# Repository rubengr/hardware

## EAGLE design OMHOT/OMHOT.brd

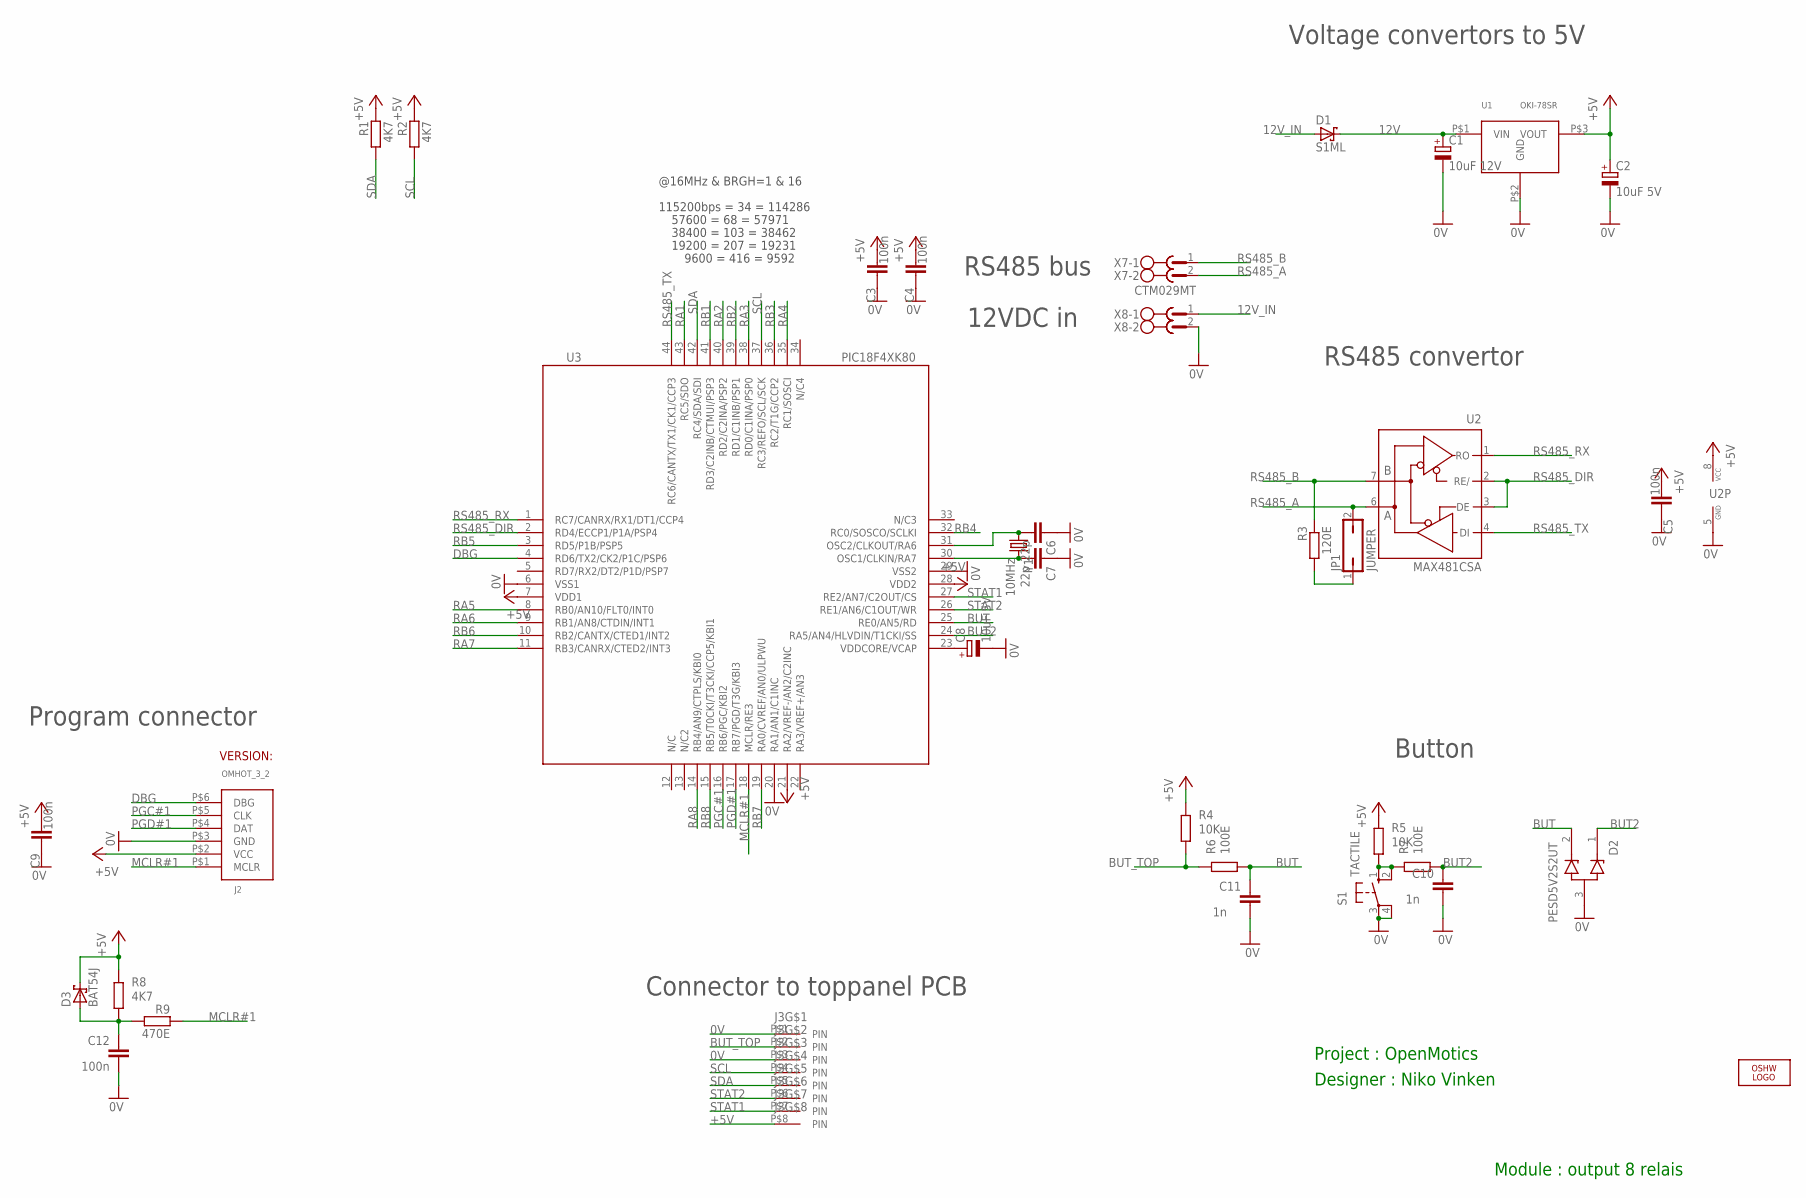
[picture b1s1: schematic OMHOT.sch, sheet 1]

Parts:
C1: 10uF 12V; 085CS_1AR
C2, C8: 10uF 5V; 085CS_1AR
C3, C4, C5, C9, C12: 100n; C0603
C6, C7: 22p; C0603
C10, C11: 1n; C0603
D1: S1ML; SOD123FL
D2: PESD5V2S2UT; SOT23
D3: BAT54J; SOD323_REFLOW
J2: PROG_CON; PROG_CON_WITH_VERSION
J3: 8PIN_CON_AMP
JP1: JUMPER; JP1
LOGO2: OSHW_LOGO_FILLX0150-NT; OSHW_FILLX150_NOTEXT
R1, R2, R8: 4K7; R0603
R3: 120E; R1206
R4, R5: 10K; R0603
R6, R7: 100E; R0603
R9: 470E; R0603
S1: TACTILE; B3F-10XX
U1: OKI-78SR
U2: MAX481CSA; SO08
U3: PIC18F4XK80; TQFP44
X7, X8: CTM029MT
Y1: 10MHz; SM49

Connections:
0V: C1.-, C2.-, C3.2, C4.2, C5.2, C6.1, C7.1, C8.-, C9.2, C10.1, C11.1, C12.1, D2.3, J2.P$3 (GND), J3.P$1, J3.P$3, S1.3, S1.4 (P1), U1.P$2 (GND), U2.5 (GND), U3.6 (VSS1), U3.20 (RA1/AN1/C1INC), U3.29 (VSS2), X8.2; also elsewhere on the board
12V: C1.+, D1.C, U1.P$1 (VIN)
12V_IN: D1.A, X8.1
+5V: C2.+, C3.1, C4.1, C5.1, C9.1, D3.1, J2.P$2 (VCC), J3.P$8, R1.1, R2.1, R4.2, R5.2, R8.2, U1.P$3 (VOUT), U2.8 (VCC), U3.7 (VDD1), U3.21 (RA2/VREF-/AN2/C2INC), U3.28 (VDD2); also elsewhere on the board
BUT: C11.2, D2.2, R6.1, U3.25 (RE0/AN5/RD)
BUT2: C10.2, D2.1, R7.1, U3.24 (RA5/AN4/HLVDIN/T1CKI/SS)
BUT3: R5.1, R7.2, S1.1 (S), S1.2 (S1)
BUT_TOP: J3.P$2, R4.1, R6.2
DBG: J2.P$6 (DBG), U3.4 (RD6/TX2/CK2/P1C/PSP6)
MCLR#1: J2.P$1 (MCLR), R9.1, U3.18 (MCLR/RE3)
unnamed: C6.2, U3.31 (OSC2/CLKOUT/RA6), Y1.1
unnamed: C7.2, U3.30 (OSC1/CLKIN/RA7), Y1.2
unnamed: C8.+, U3.23 (VDDCORE/VCAP)
unnamed: JP1.1, R3.2
unnamed: C12.2, D3.2, R8.1, R9.2
PGC#1: J2.P$5 (CLK), U3.16 (RB6/PGC/KBI2)
PGD#1: J2.P$4 (DAT), U3.17 (RB7/PGD/T3G/KBI3)
RA1: U3.43 (RC5/SDO); also elsewhere on the board
RA2: U3.40 (RD2/C2INA/PSP2); also elsewhere on the board
RA3: U3.38 (RD0/C1INA/PSP0); also elsewhere on the board
RA4: U3.35 (RC1/SOSCI); also elsewhere on the board
RA5: U3.8 (RB0/AN10/FLT0/INT0); also elsewhere on the board
RA6: U3.9 (RB1/AN8/CTDIN/INT1); also elsewhere on the board
RA7: U3.11 (RB3/CANRX/CTED2/INT3); also elsewhere on the board
RA8: U3.14 (RB4/AN9/CTPLS/KBI0); also elsewhere on the board
RB1: U3.41 (RD3/C2INB/CTMUI/PSP3); also elsewhere on the board
RB2: U3.39 (RD1/C1INB/PSP1); also elsewhere on the board
RB3: U3.36 (RC2/T1G/CCP2); also elsewhere on the board
RB4: U3.32 (RC0/SOSCO/SCLKI); also elsewhere on the board
RB5: U3.3 (RD5/P1B/PSP5); also elsewhere on the board
RB6: U3.10 (RB2/CANTX/CTED1/INT2); also elsewhere on the board
RB7: U3.19 (RA0/CVREF/AN0/ULPWU); also elsewhere on the board
RB8: U3.15 (RB5/T0CKI/T3CKI/CCP5/KBI1); also elsewhere on the board
RS485_A: JP1.2, U2.6 (A), X7.2
RS485_B: R3.1, U2.7 (B), X7.1
RS485_DIR: U2.2 (RE/), U2.3 (DE), U3.2 (RD4/ECCP1/P1A/PSP4)
RS485_RX: U2.1 (RO), U3.1 (RC7/CANRX/RX1/DT1/CCP4)
RS485_TX: U2.4 (DI), U3.44 (RC6/CANTX/TX1/CK1/CCP3)
SCL: J3.P$4, R2.2, U3.37 (RC3/REFO/SCL/SCK)
SDA: J3.P$5, R1.2, U3.42 (RC4/SDA/SDI)
STAT1: J3.P$7, U3.27 (RE2/AN7/C2OUT/CS)
STAT2: J3.P$6, U3.26 (RE1/AN6/C1OUT/WR)

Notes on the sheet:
Project : OpenMotics
Designer : Niko Vinken
Module : output 8 relais
Program connector
RS485 convertor
Connector to toppanel PCB
Button
@16MHz & BRGH=1 & 16
115200bps = 34 = 114286
38400 = 103 = 38462
9600 = 416 = 9592
19200 = 207 = 19231
57600 = 68 = 57971
Voltage convertors to 5V
RS485 bus
12VDC in

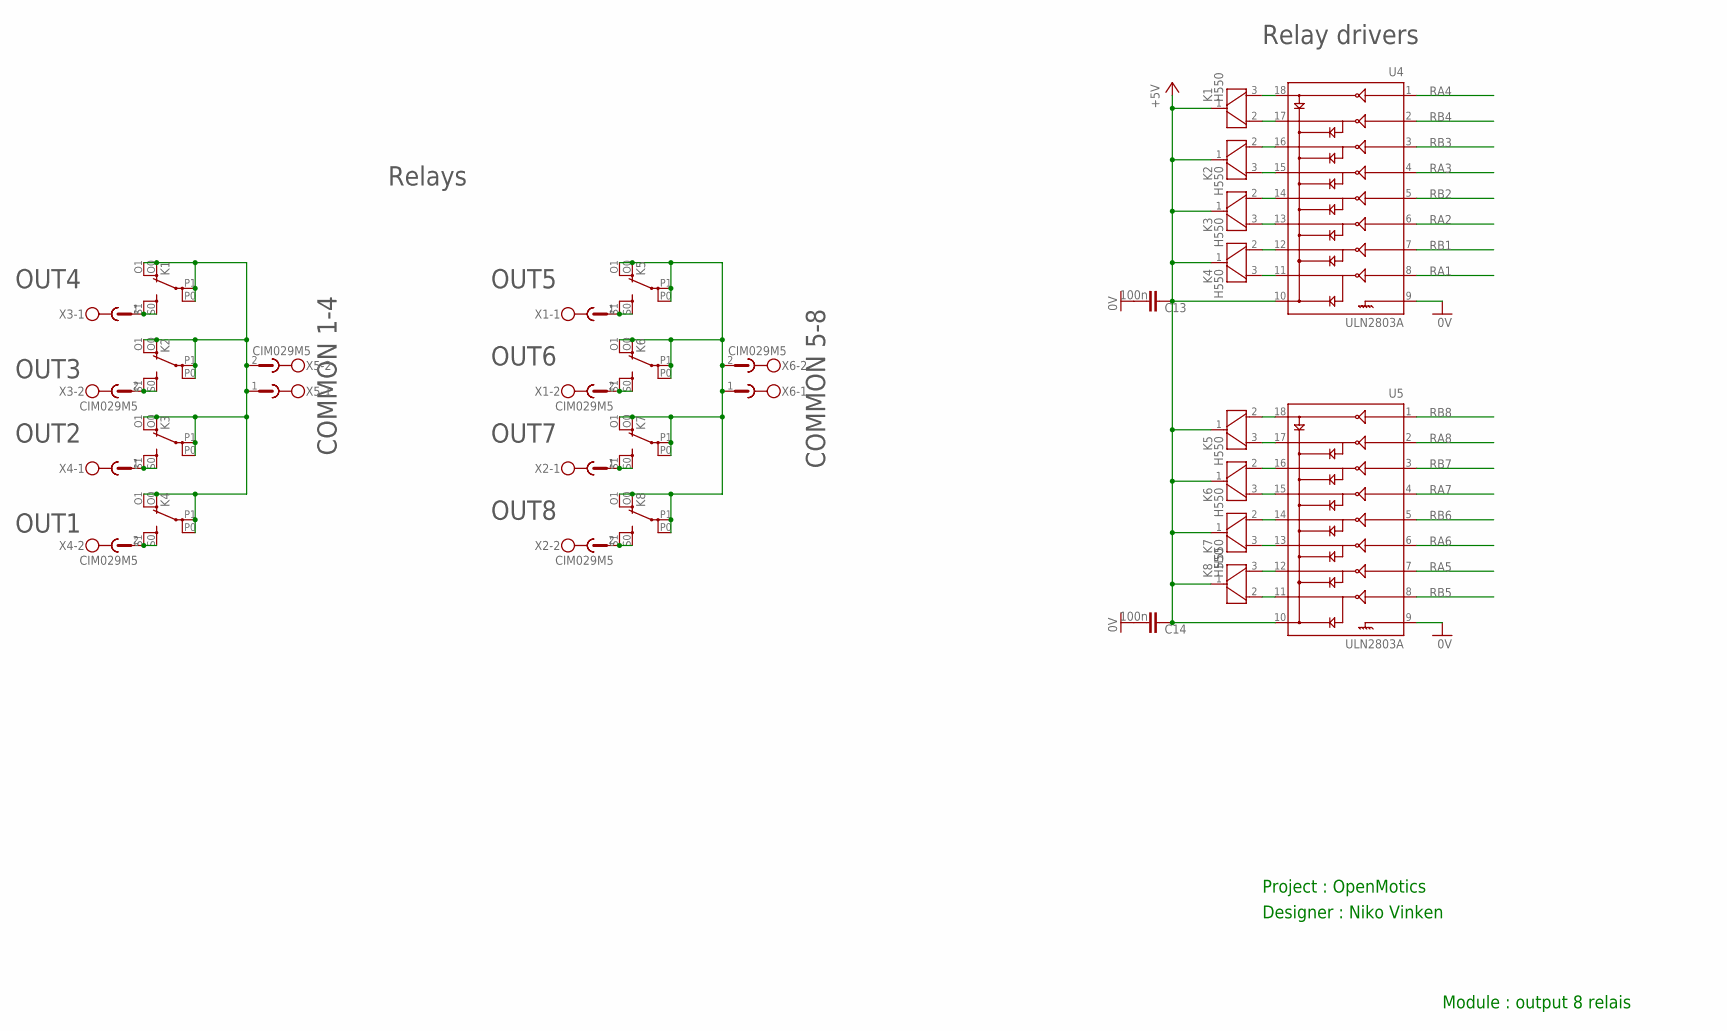
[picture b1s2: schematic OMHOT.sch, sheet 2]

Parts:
C13, C14: 100n; C0603
K1, K2, K3, K4, K5, K6, K7, K8: H550
U4, U5: ULN2803A; SOIC18
X1, X2, X3, X4, X5, X6: CIM029M5

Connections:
0V: C13.1, C14.1, U4.9, U5.9; also elsewhere on the board
+5V: C13.2, C14.2, K1.1, K2.1, K3.1, K4.1, K5.1, K6.1, K7.1, K8.1, U4.10, U5.10; also elsewhere on the board
unnamed: K5.S0 (S), K5.S1 (S), X1.1
unnamed: K3.S0 (S), K3.S1 (S), X4.1
unnamed: K4.S0 (S), K4.S1 (S), X4.2
unnamed: K6.S0 (S), K6.S1 (S), X1.2
unnamed: K4.3, U4.11
unnamed: K4.2, U4.12
unnamed: K1.S0 (S), K1.S1 (S), X3.1
unnamed: K3.3, U4.13
unnamed: K7.S0 (S), K7.S1 (S), X2.1
unnamed: K8.S0 (S), K8.S1 (S), X2.2
unnamed: K1.O0 (O), K1.O1 (O), K1.P0, K1.P1, K2.O0 (O), K2.O1 (O), K2.P0, K2.P1, K3.O0 (O), K3.O1 (O), K3.P0, K3.P1, K4.O0 (O), K4.O1 (O), K4.P0, K4.P1, X5.1, X5.2
unnamed: K2.S0 (S), K2.S1 (S), X3.2
unnamed: K3.2, U4.14
unnamed: K2.3, U4.15
unnamed: K2.2, U4.16
unnamed: K1.3, U4.18
unnamed: K1.2, U4.17
unnamed: K5.3, U5.17
unnamed: K5.O0 (O), K5.O1 (O), K5.P0, K5.P1, K6.O0 (O), K6.O1 (O), K6.P0, K6.P1, K7.O0 (O), K7.O1 (O), K7.P0, K7.P1, K8.O0 (O), K8.O1 (O), K8.P0, K8.P1, X6.1, X6.2
unnamed: K5.2, U5.18
unnamed: K6.3, U5.15
unnamed: K6.2, U5.16
unnamed: K7.3, U5.13
unnamed: K7.2, U5.14
unnamed: K8.3, U5.12
unnamed: K8.2, U5.11
RA1: U4.8; also elsewhere on the board
RA2: U4.6; also elsewhere on the board
RA3: U4.4; also elsewhere on the board
RA4: U4.1; also elsewhere on the board
RA5: U5.7; also elsewhere on the board
RA6: U5.6; also elsewhere on the board
RA7: U5.4; also elsewhere on the board
RA8: U5.2; also elsewhere on the board
RB1: U4.7; also elsewhere on the board
RB2: U4.5; also elsewhere on the board
RB3: U4.3; also elsewhere on the board
RB4: U4.2; also elsewhere on the board
RB5: U5.8; also elsewhere on the board
RB6: U5.5; also elsewhere on the board
RB7: U5.3; also elsewhere on the board
RB8: U5.1; also elsewhere on the board

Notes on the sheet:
Project : OpenMotics
Designer : Niko Vinken
Module : output 8 relais
Relay drivers
Relays
OUT4
OUT3
OUT2
OUT1
OUT5
OUT6
OUT7
OUT8
COMMON 1-4
COMMON 5-8

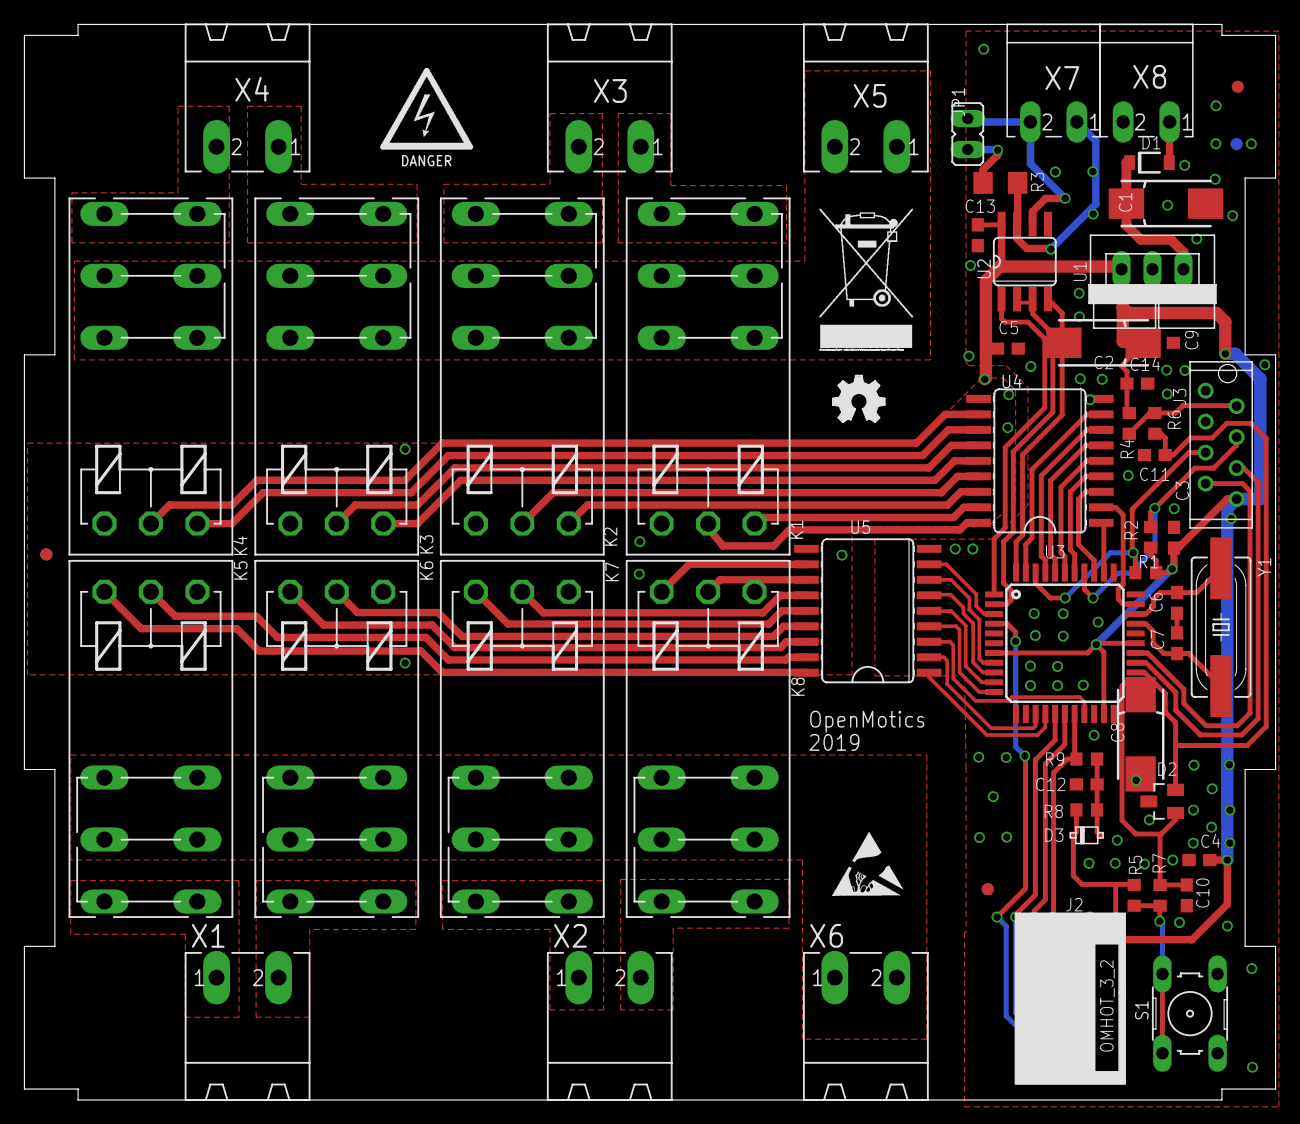
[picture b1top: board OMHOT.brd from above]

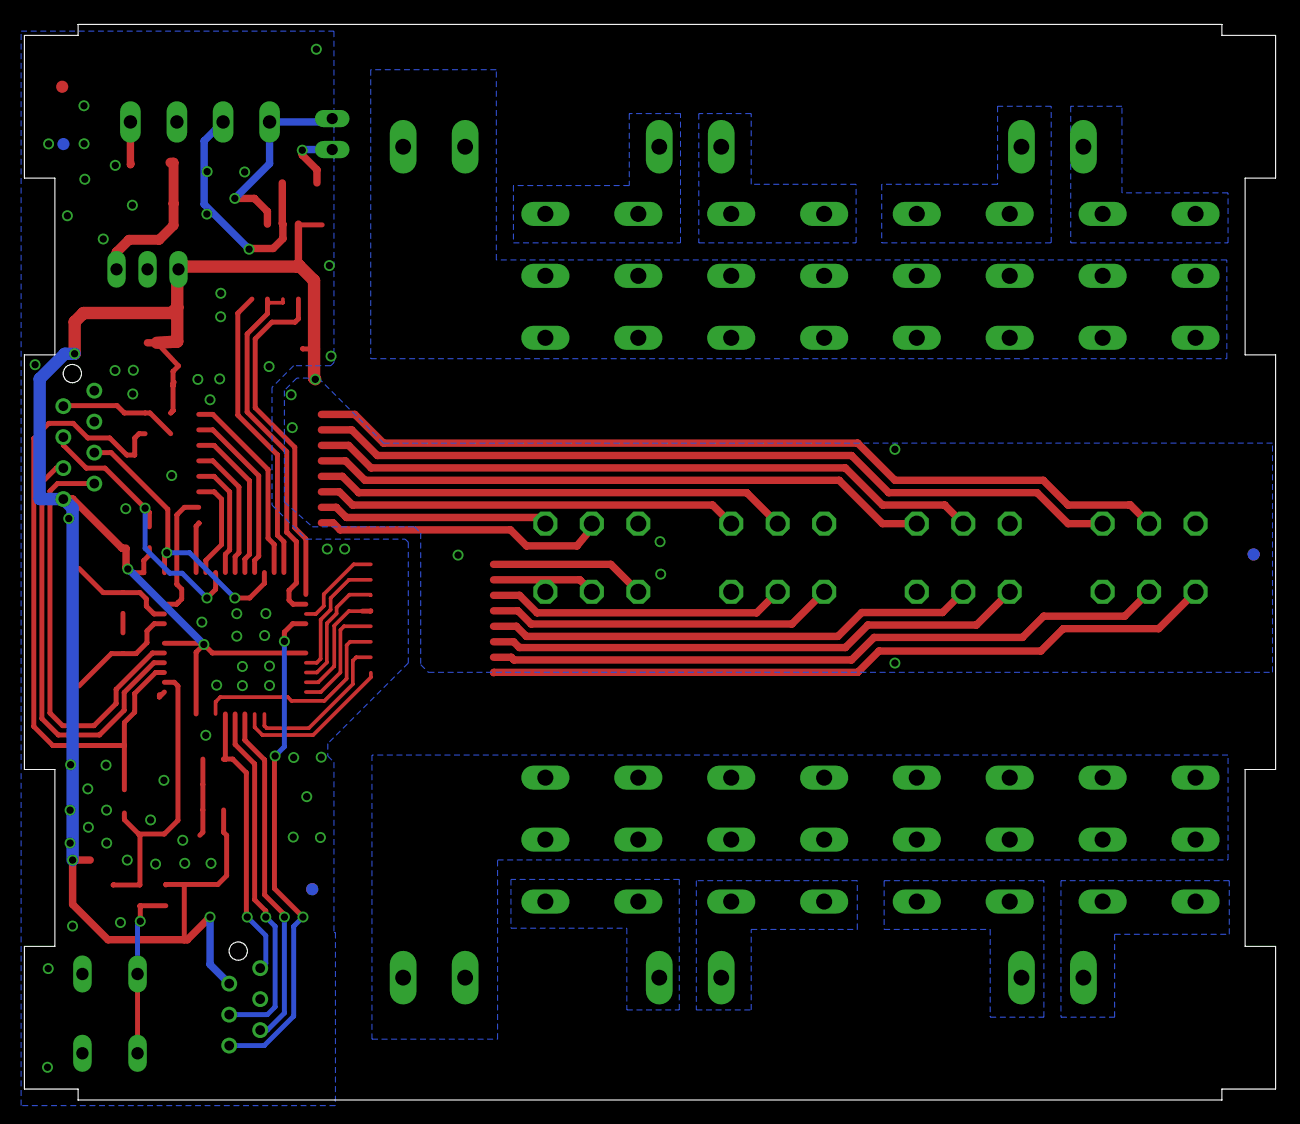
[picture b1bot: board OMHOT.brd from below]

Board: 2 copper layers, 102.6 x 88.2 mm, 63 parts (3 on the bottom side), 68 nets.

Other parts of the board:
U$1, U$2, U$3, U$5, U$6, U$12: FIDUCIAL_G10
U$4: CNMB/6; CNMB/6-
U$8: DISPOSAL-SYMBOL; DISPOSAL
U$10: ESD
U$11: HIGH-VOLTAGE

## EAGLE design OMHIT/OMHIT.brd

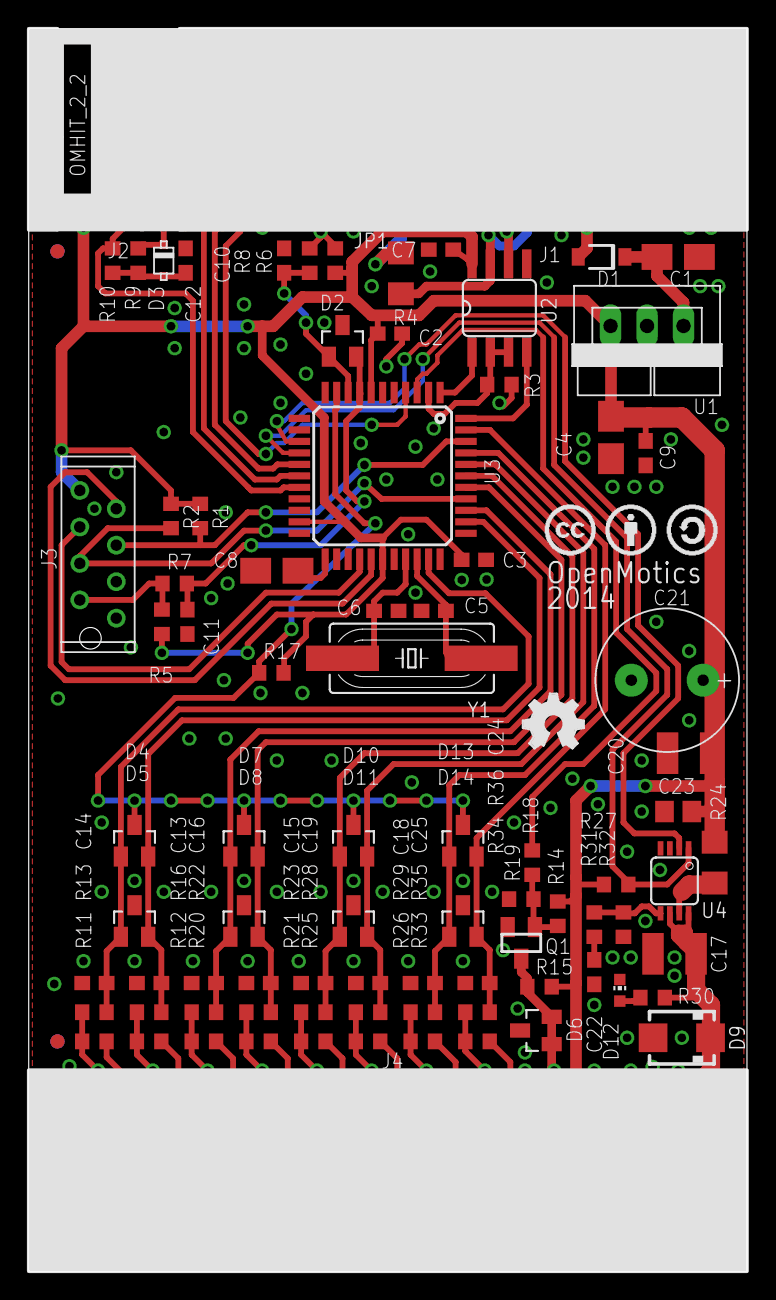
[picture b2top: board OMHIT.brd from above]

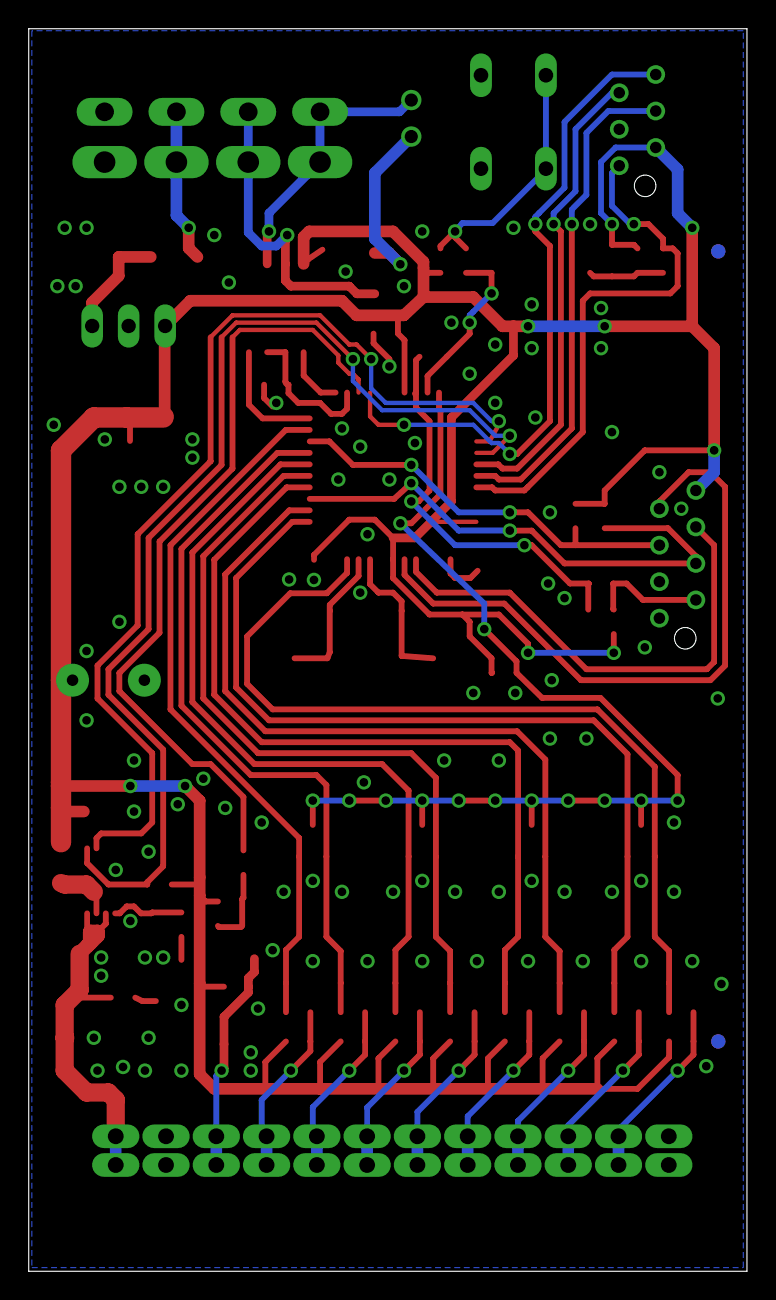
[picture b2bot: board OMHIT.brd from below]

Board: 2 copper layers, 50.0 x 86.5 mm, 94 parts (2 on the bottom side), 53 nets.

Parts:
C1: 10uF 12V; A3216-18W
C2, C3, C7, C9, C12, C22: 100n; C0603
C4: 10uF 5V; A3216-18W
C5, C6: 22p; C0603
C8: 10u; A3216-18W
C10, C11, C13, C14, C15, C16, C18, C19, C24, C25: 1n; C0603
C17, C20: 22uF; C1210K
C21: 1000uF; ELCO10MM
C23: 1u; C0805
D1: S1ML; SOD123FL
D2, D5, D8, D11, D14: PESD5V2S2UT; SOT23
D3: BAT54J; SOD323_REFLOW
D4, D7, D10, D13: BAT54A; SOT23
D6: PESD3V3S2UAT; SOT23
D9: SMAJ6.0A; SMA
D12: LGQ971; CHIP-LED0603
J1: PTDA_1.5_4-PH_5.0; PTDA_1.5_X-PH_5.0
J2: PROG_CON_WITH_VERSION
J3: 8PIN_CON_AMP
J4: PTDA_1.5_12-PH_3.5; PTDA_1.5_X-PH_3.5
JP1: JP1S
LOGO2: OSHW_LOGO_FILLX0150-NT; OSHW_FILLX150_NOTEXT
Q1: PMBF170; SUPER-SOT3
R1, R2, R9: 4K7; R0603
R3, R5, R6, R11, R12, R14, R15, R17, R19, R20, R21, R25, R26, R33, R34: 10K; R0603
R4: 120E; R1206
R7, R8: 100E; R0603
R10, R32: 470R; R0603
R13, R16, R22, R23, R28, R29, R35, R36: 100R; R0603
R18: 470E; R0603
R24: 0R; R1206
R27: 100K; R0603
R30: 560R; R0603
R31: 232R; R0603
S1: B3F-10XX
U1: OKI-78SR
U2: MAX481CSA; SO08
U3: PIC18F4XK80; TQFP44
U4: MIC2548-1YMM; MSOP08
U$1, U$2, U$3, U$12: FIDUCIAL_G10
U$4: CNMB/3; CNMB/3-
U$5: CC_BY_SA
Y1: 10MHz; SM49

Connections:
0V: C1.-, C2.2, C3.2, C4.-, C5.1, C6.1, C7.2, C8.-, C9.2, C10.1, C11.1, C12.1, C13.2, C14.2, C15.2, C16.2, C17.2, C18.2, C19.2, C20.2, C21.-, C22.1, C23.1, C24.2, C25.2, D2.3, D5.3, D6.3, D8.3, D9.A, D11.3, D12.C, D14.3, J1.P$4, J1.P$8, J2.P$3, J3.P$1, J3.P$3, J4.P$2, J4.P$12, J4.P$14, J4.P$24, Q1.2, R3.1, R19.1, R32.1, S1.3, S1.4, U1.P$2, U2.5, U3.6, U3.20, U3.29, U4.3
5V_OUT: C17.1, D9.K, J4.P$1, J4.P$13, R30.2, U4.6, U4.8
12V: C1.+, D1.C, U1.P$1
12V_IN: D1.A, J1.P$3, J1.P$7
+5V: C2.1, C3.1, C4.+, C7.1, C9.1, C20.1, C21.+, C23.2, D3.1, J2.P$2, J3.P$8, R1.1, R2.1, R5.2, R6.2, R9.2, R11.2, R12.2, R14.2, R15.2, R17.2, R20.2, R21.2, R24.1, R25.2, R26.2, R27.2, R33.2, R34.2, U1.P$3, U2.8, U3.7, U3.21, U3.28
BUT: C11.2, D2.2, R7.1, U3.8
BUT1: R6.1, R8.2, S1.1, S1.2
BUT2: C10.2, D2.1, R8.1, U3.9
BUT_TOP: J3.P$2, R5.1, R7.2
CHECK_SC: U3.14, U4.2
CLK: D6.1, D6.2, J4.P$3, J4.P$15, Q1.3, R15.1
CLOCK: R18.2, U3.3
DBG: J2.P$6, U3.4
IN1: J4.P$11, J4.P$23, R11.1, R13.2
IN2: J4.P$10, J4.P$22, R12.1, R16.2
IN3: J4.P$9, J4.P$21, R20.1, R22.2
IN4: J4.P$8, J4.P$20, R21.1, R23.2
IN5: J4.P$7, J4.P$19, R25.1, R28.2
IN6: J4.P$6, J4.P$18, R26.1, R29.2
IN7: J4.P$5, J4.P$17, R33.1, R35.2
IN8: J4.P$4, J4.P$16, R34.1, R36.2
INPUT1: C14.1, D4.1, D5.1, R13.1, U3.32
INPUT2: C13.1, D4.2, D5.2, R16.1, U3.35
INPUT3: C16.1, D7.1, D8.1, R22.1, U3.36
INPUT4: C15.1, D7.2, D8.2, R23.1, U3.38
INPUT5: C19.1, D10.1, D11.1, R28.1, U3.39
INPUT6: C18.1, D10.2, D11.2, R29.1, U3.40
INPUT7: C25.1, D13.1, D14.1, R35.1, U3.41
INPUT8: C24.1, D13.2, D14.2, R36.1, U3.43
INTR_BUTTONS: D4.3, D7.3, D10.3, D13.3, R17.1, U3.10
MCLR#1: J2.P$1, R10.1, U3.18
unnamed: JP1.1, R4.2
unnamed: C12.2, D3.2, R9.1, R10.2
unnamed: Q1.1, R14.1, R18.1, R19.2
unnamed: C5.2, U3.31, Y1.1
unnamed: C6.2, U3.30, Y1.2
unnamed: C8.+, U3.23
unnamed: D12.A, R30.1
unnamed: R24.2, U4.7
unnamed: R31.2, R32.2, U4.5
unnamed: C22.2, R31.1
PGC#1: J2.P$5, U3.16
PGD#1: J2.P$4, U3.17
POWER_ON: R27.1, U3.15, U4.1
RS485_A: J1.P$1, J1.P$5, JP1.2, U2.6
RS485_B: J1.P$2, J1.P$6, R4.1, U2.7
RS485_DIR: R3.2, U2.2, U2.3, U3.2
RS485_RX: U2.1, U3.1
RS485_TX: U2.4, U3.44
SCL: J3.P$4, R2.2, U3.37
SDA: J3.P$5, R1.2, U3.42
STAT1: J3.P$7, U3.27
STAT2: J3.P$6, U3.26

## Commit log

2019-10-15 Added dimensions for new enclosure
2019-11-05 Added my version and firmware
2020-06-14 Added files with correct version of gateway
